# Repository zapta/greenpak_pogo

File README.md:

# GreenPAK Programming Pogo Probe

This project provides a standard footprint and a Pogo Probe for in-circuit programming of Renesas GreenPAK 
devices. This can be used for example in production after populating the board with factory reset GreenPAK devices.

<br>

Highlights:

* Small footprint.
* In expensive (e.g. compared to Tag Connect)
* Can be used with any QWIIC masters as a probrammer.
* Can provide power to the programmed device.
* A single programming socket can support multiple GreenPAK devices on the same board.

# Schematic

# Pogo pins

We use common pogo pins from Aliexpress, the 5mm ones from https://www.aliexpress.us/item/3256803830386881.html. The diagram belows shows the advertised dimensions on Aliexpress, note that there are two 3.5mm dimensions, the longer of the two is actually 5mm. Also, the diameter of the base is 2mm.

# Connector

The connector is JST SH 1.0mm 4pin, SMD, horizontal, and is common on Aliexpress as well as short cables with matching QWIIC connectors on both ends. This is the same connector that is used by the QWIIC and STEMMA QT eco system and follows their pinout.  

| :warning: WARNING          |
|:---------------------------|
| The connecor follows the QWIIC pinout conventions and which are different from the pinout of the Renesas programmer.  If you are using the Pogo Probe with the Renesas programmer, pay attention to the wiring.    |

# Power jumper

The solder jumper on the Pogo Probe allows to connect or disconnect the VCC power of the programmer and the programmed board. By default it's disconnected and if needed, you can connect it with a drop of solder. 

# Pullup resistors

The Pogo Probe has two footprints for pullup resistors for the SDA and SCL signals respectivly. Populating them with 5K to 10K 0402 resistors should work well in most cases. If the circuit being programmed or the I2C master used to program already contain pullup resistors (it should, since the SDA and SCL GreenPAK inputs are not pulled up internally), they can be ommited.

# Programming socket

Kicad comaptible symbol and footprint for the programming socket are available in the kicad directory of this repository.

<br>

Schematic symbol:

<br>

PCB footprint:

<br>

PCB pads dimensions:

Top view, in mm. 

# Programming

We use a boards that are compatible with the Python ``i2c_adapter`` packge and the Python ``greenpak`` to program the boards. For example, if you use the SparkFun Pro Micro - RP2040 which contains a QWIIC connector, you can use a standard QWIIC cable to connect it to the Pogo Probe. Programming typically taks about 1 sec such that placing and holding the probe and hitting the program key is straight forward.

# Pin pattern

This pin patter was selected with these goals

* Small footprint.
* Non symetric, with only one 'right way' to connect it.
* Rounded dimensions in mm, vs mills. Introduced in V02.

# PCB order

The gerber file of the Pogo Probe is available under the JLCPCB directory. Smaller boards like this typically benefit from a thinner PCB (e.g. 1mm instead of 1.6mm) but we use 1.6mm for better mechanical support and easier holding.

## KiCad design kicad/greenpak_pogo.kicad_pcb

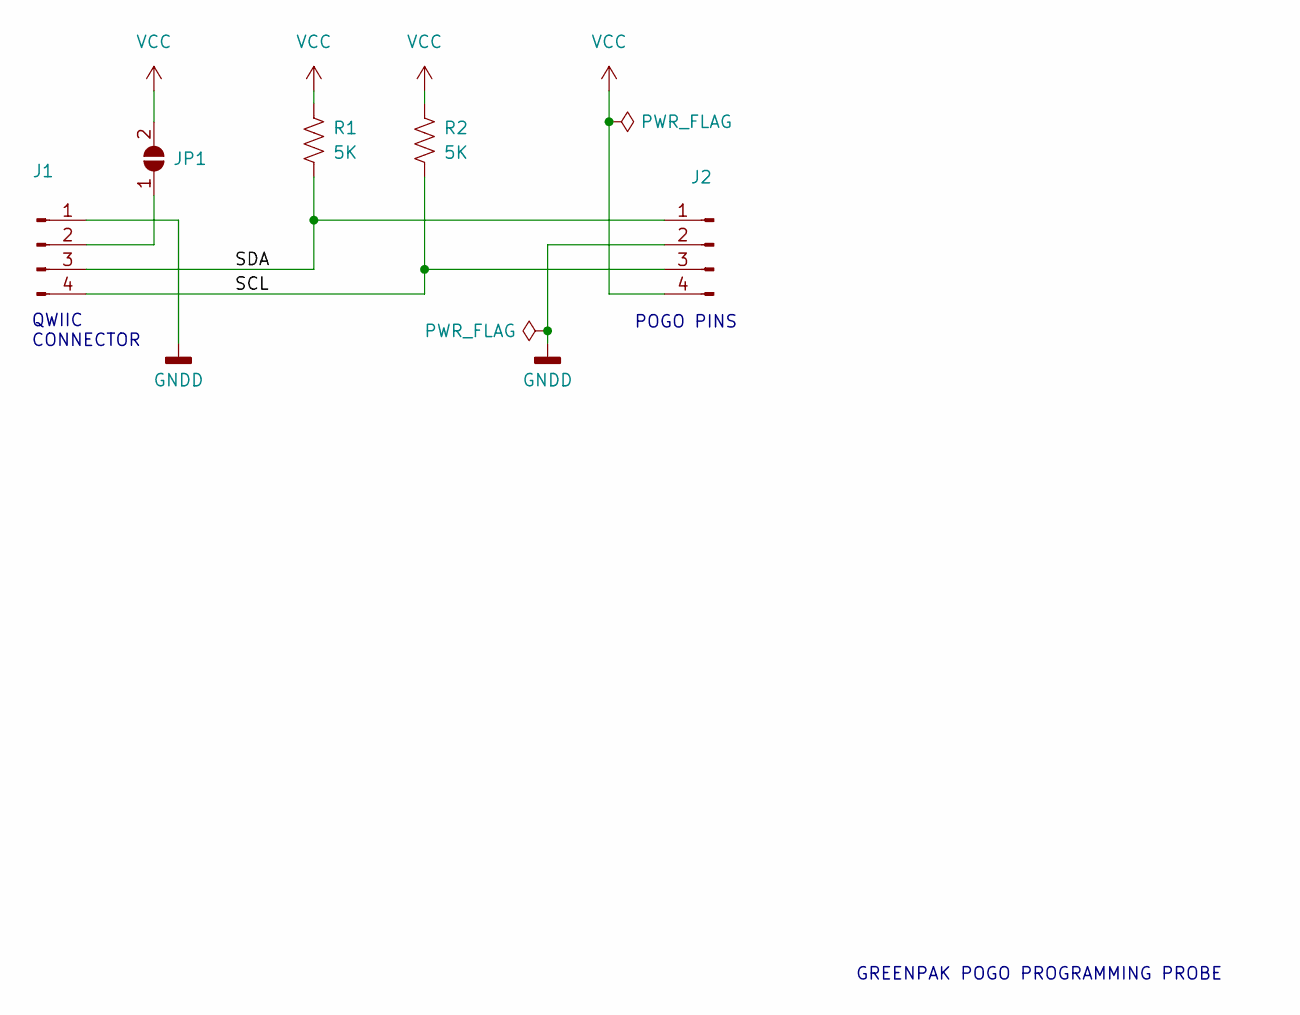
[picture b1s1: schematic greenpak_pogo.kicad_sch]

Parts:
J1: JST_SH_SM04B-SRSS-TB_1x04-1MP_P1.00mm_Horizontal
J2: GREENPAK_POGO_PINS
JP1: SOLDER_JUMPER
R1, R2: 5K; R_0402_1005Metric

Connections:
/SCL: J1.4, J2.3, R2.2
/SDA: J1.3, J2.1, R1.2
GNDD: J1.1, J2.2
unnamed: J1.2, JP1.1 (A)
VCC: J2.4, JP1.2 (B), R1.1, R2.1

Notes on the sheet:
GREENPAK POGO PROGRAMMING PROBE
QWIIC CONNECTOR
POGO PINS

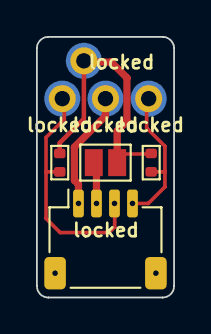
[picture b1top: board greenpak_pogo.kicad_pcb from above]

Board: 2 copper layers, 7.6 x 14.5 mm, 6 parts (1 on the bottom side), 5 nets.

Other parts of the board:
G*: LOGO; QWIIC_logo_6mm

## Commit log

2024-01-24 Moved pogo directory to the new repository.
2024-01-24 Cleaned up post project name change to greenpak_pogo.
2024-01-24 Added 3D models.
2024-01-24 Fixed the appearance of the QWIIC connector 3d model.
2024-01-24 Added 3d models of pins.
2024-01-24 Tweak the pogo PCB boundary.
2024-01-24 Added pcb rendering.
2024-01-24 Added documentation.
2024-01-24 Updated the documentation.
2024-01-24 Fix a typo.
2024-01-24 Added to the pogo probe pullup resistors.
2024-01-24 Updated doc.
2024-01-24 Updated documentation.
2024-01-25 Changed doc image references to local.
2024-02-05 Updated pogo socket to new dimensions.
2024-02-05 Added TODO.txt
2024-02-05 Added schematic.
2024-02-05 Generated gervers.
2024-02-05 Added schematic to the doc.
2024-02-05 Increased VCC trace width and regenerated gerbers.
2024-02-05 Tweaked the silkscreen of the pogo socket.
